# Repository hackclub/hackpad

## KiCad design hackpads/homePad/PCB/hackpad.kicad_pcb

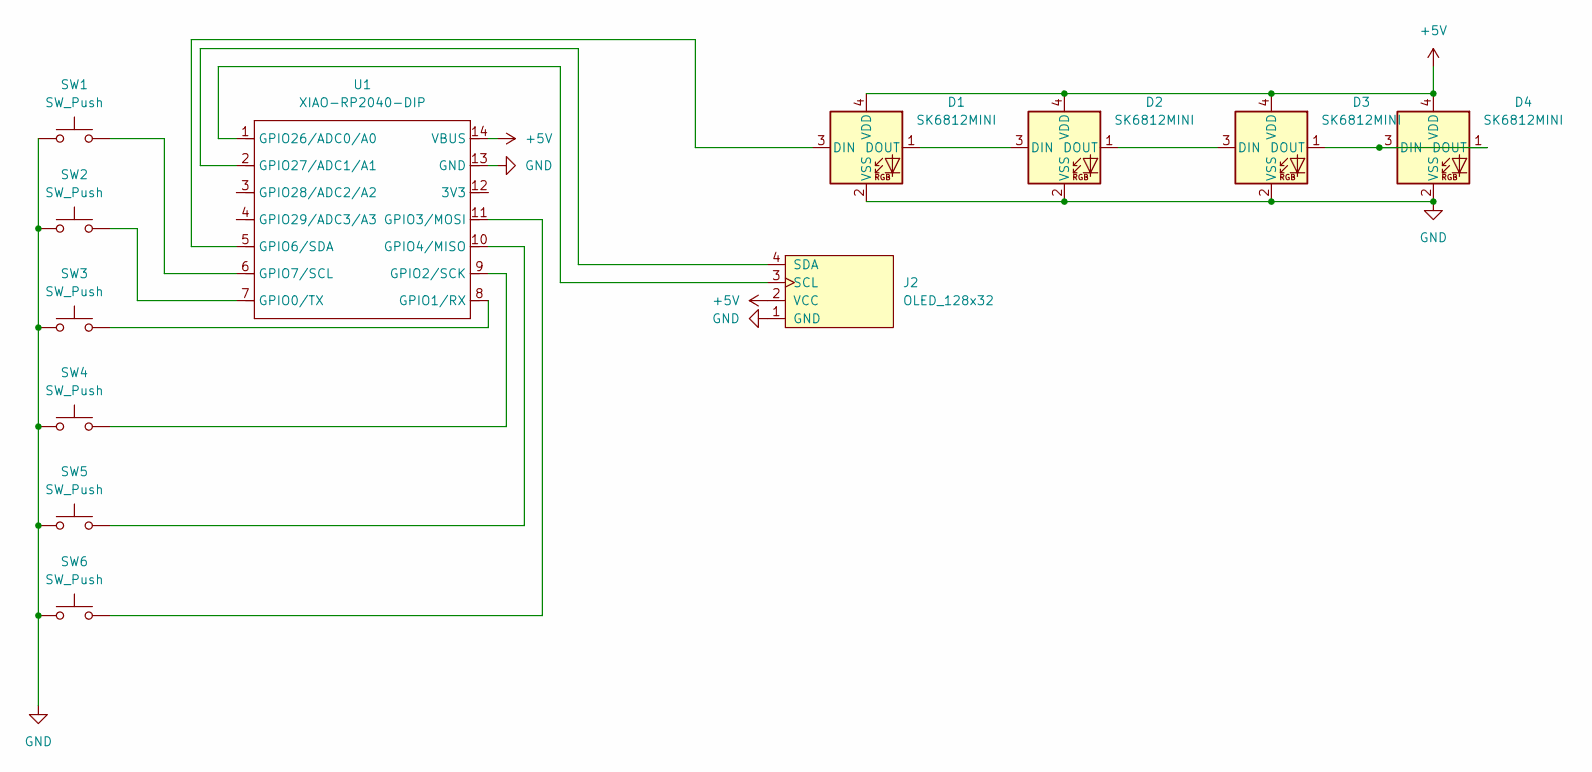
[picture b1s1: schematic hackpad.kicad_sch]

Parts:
D1, D2, D3, D4: SK6812MINI; LED_SK6812MINI_PLCC4_3.5x3.5mm_P1.75mm
J2: OLED_128x32
SW1, SW2, SW3, SW4, SW5, SW6: SW_Push; SW_Cherry_MX_1.00u_PCB
U1: XIAO-RP2040-DIP

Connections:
+5V: D1.4 (VDD), D2.4 (VDD), D3.4 (VDD), D4.4 (VDD), J2.2 (VCC), U1.14 (VBUS)
GND: D1.2 (VSS), D2.2 (VSS), D3.2 (VSS), D4.2 (VSS), J2.1 (GND), SW1.1, SW2.1, SW3.1, SW4.1, SW5.1, SW6.1, U1.13 (GND)
unnamed: D1.3 (DIN), U1.5 (GPIO6/SDA)
unnamed: D1.1 (DOUT), D2.3 (DIN)
unnamed: D2.1 (DOUT), D3.3 (DIN)
unnamed: D3.1 (DOUT), D4.1 (DOUT), D4.3 (DIN)
unnamed: J2.3 (SCL), U1.1 (GPIO26/ADC0/A0)
unnamed: J2.4 (SDA), U1.2 (GPIO27/ADC1/A1)
unnamed: SW2.2, U1.7 (GPIO0/TX)
unnamed: SW3.2, U1.8 (GPIO1/RX)
unnamed: SW4.2, U1.9 (GPIO2/SCK)
unnamed: SW6.2, U1.11 (GPIO3/MOSI)
unnamed: SW5.2, U1.10 (GPIO4/MISO)
unnamed: SW1.2, U1.6 (GPIO7/SCL)

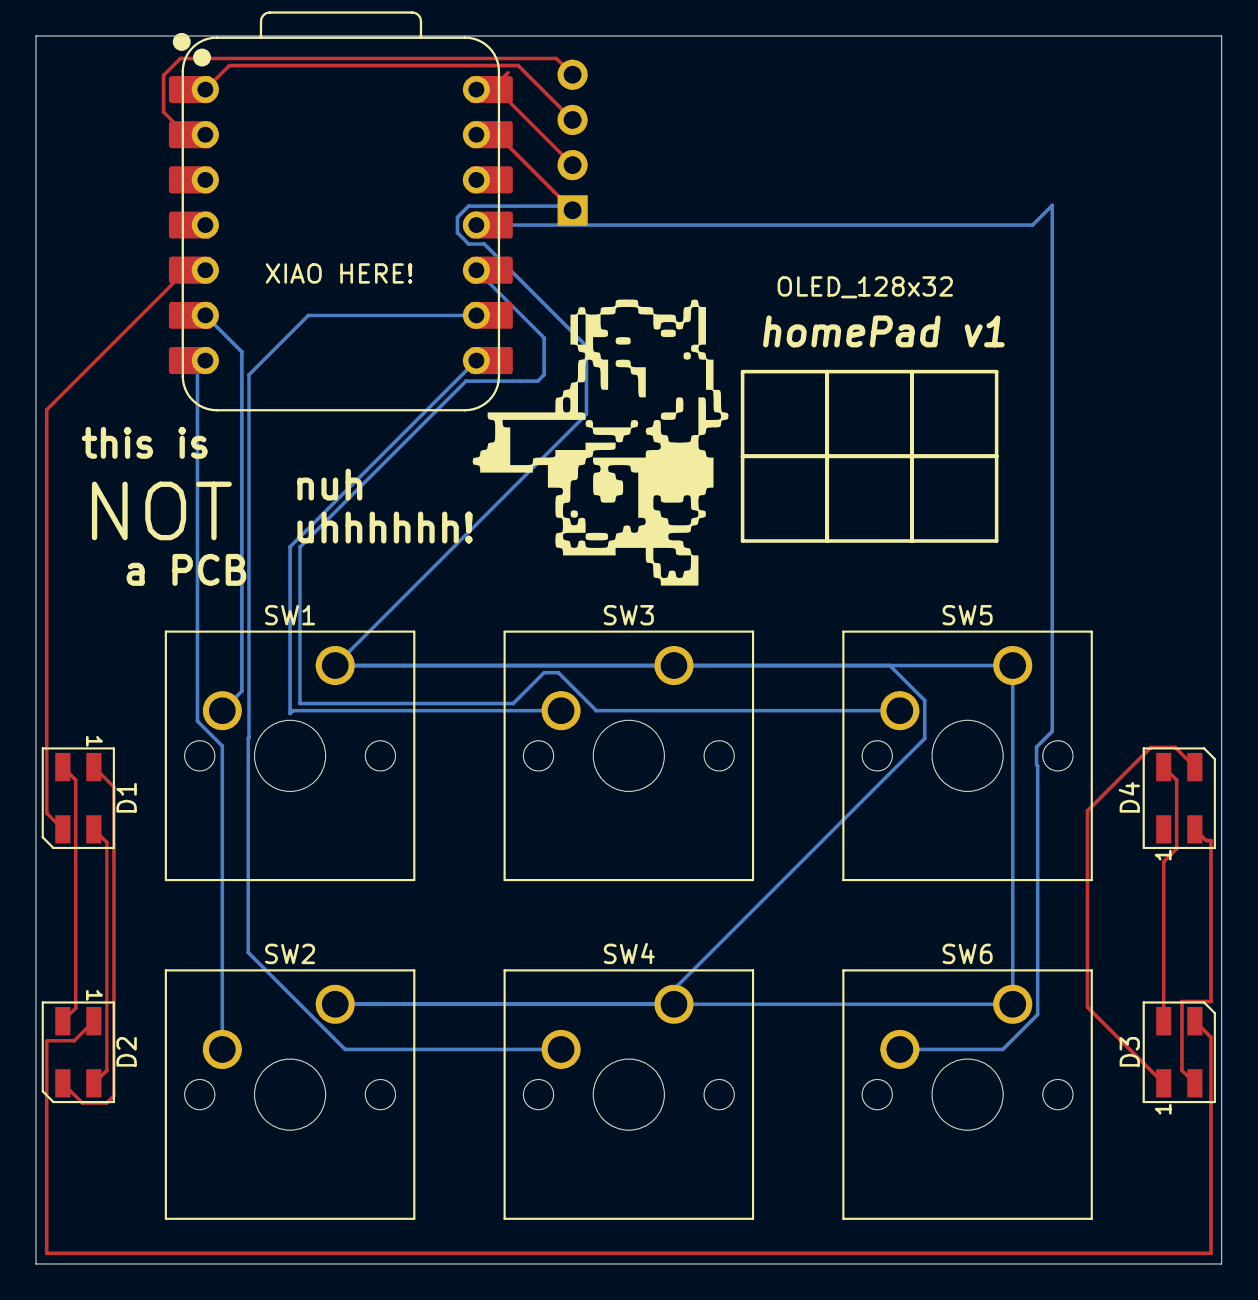
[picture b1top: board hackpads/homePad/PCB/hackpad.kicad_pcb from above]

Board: 2 copper layers, 66.7 x 69.1 mm, 12 parts (0 on the bottom side), 14 nets.

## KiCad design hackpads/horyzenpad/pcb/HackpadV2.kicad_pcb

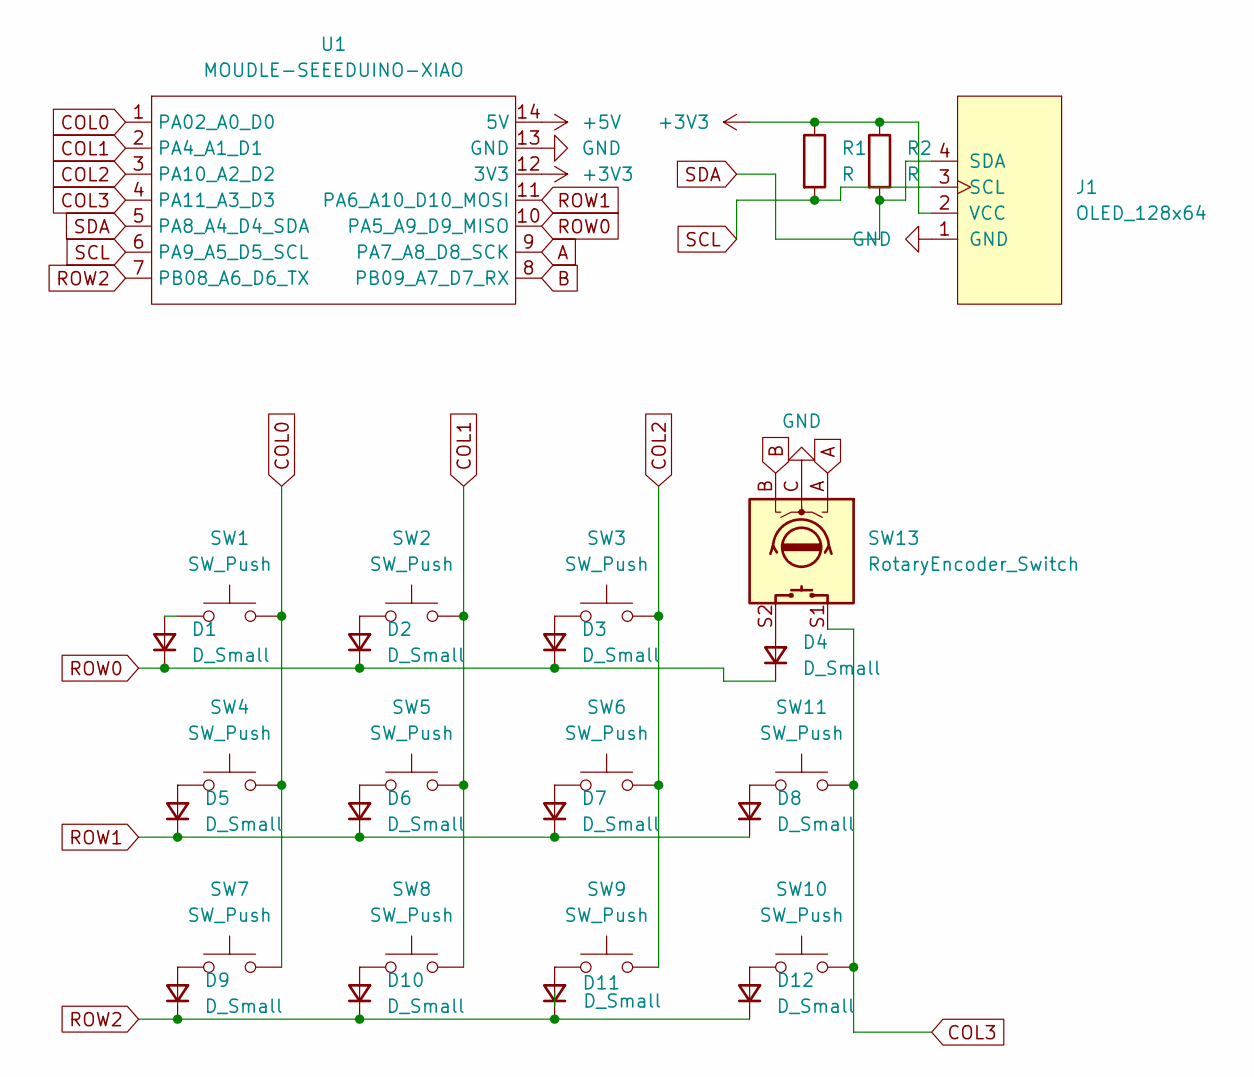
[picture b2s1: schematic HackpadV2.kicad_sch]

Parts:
D1, D2, D3, D4, D5, D6, D7, D8, D9, D10, D11, D12: D_Small; Diode_DO-35
J1: OLED_128x64
R1, R2: R; R_Axial_DIN0204_L3.6mm_D1.6mm_P7.62mm_Horizontal
SW1, SW2, SW3, SW4, SW5, SW6, SW7, SW8, SW9, SW10, SW11: SW_Push; SW_Cherry_MX_1.00u_PCB
SW13: RotaryEncoder_Switch; RotaryEncoder_Alps_EC11E-Switch_Vertical_H20mm
U1: MOUDLE-SEEEDUINO-XIAO; XIAO-Generic-Hybrid-14P-2.54-21X17.8MM

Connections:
+3V3: J1.2 (VCC), R1.1, R2.1, U1.12 (3V3)
+5V: U1.14 (5V)
A: SW13.A, U1.9 (PA7_A8_D8_SCK)
B: SW13.B, U1.8 (PB09_A7_D7_RX)
COL0: SW1.2, SW4.2, SW7.2, U1.1 (PA02_A0_D0)
COL1: SW2.2, SW5.2, SW8.2, U1.2 (PA4_A1_D1)
COL2: SW3.2, SW6.2, SW9.2, U1.3 (PA10_A2_D2)
COL3: SW10.2, SW11.2, SW13.S1, U1.4 (PA11_A3_D3)
GND: J1.1 (GND), SW13.C, U1.13 (GND)
unnamed: D1.2 (A), SW1.1
unnamed: D2.2 (A), SW2.1
unnamed: D3.2 (A), SW3.1
unnamed: D4.2 (A), SW13.S2
unnamed: D5.2 (A), SW4.1
unnamed: D6.2 (A), SW5.1
unnamed: D7.2 (A), SW6.1
unnamed: D8.2 (A), SW11.1
unnamed: D9.2 (A), SW7.1
unnamed: D10.2 (A), SW8.1
unnamed: D11.2 (A), SW9.1
unnamed: D12.2 (A), SW10.1
ROW0: D1.1 (K), D2.1 (K), D3.1 (K), D4.1 (K), U1.10 (PA5_A9_D9_MISO)
ROW1: D5.1 (K), D6.1 (K), D7.1 (K), D8.1 (K), U1.11 (PA6_A10_D10_MOSI)
ROW2: D9.1 (K), D10.1 (K), D11.1 (K), D12.1 (K), U1.7 (PB08_A6_D6_TX)
SCL: J1.3 (SCL), R1.2, U1.6 (PA9_A5_D5_SCL)
SDA: J1.4 (SDA), R2.2, U1.5 (PA8_A4_D4_SDA)

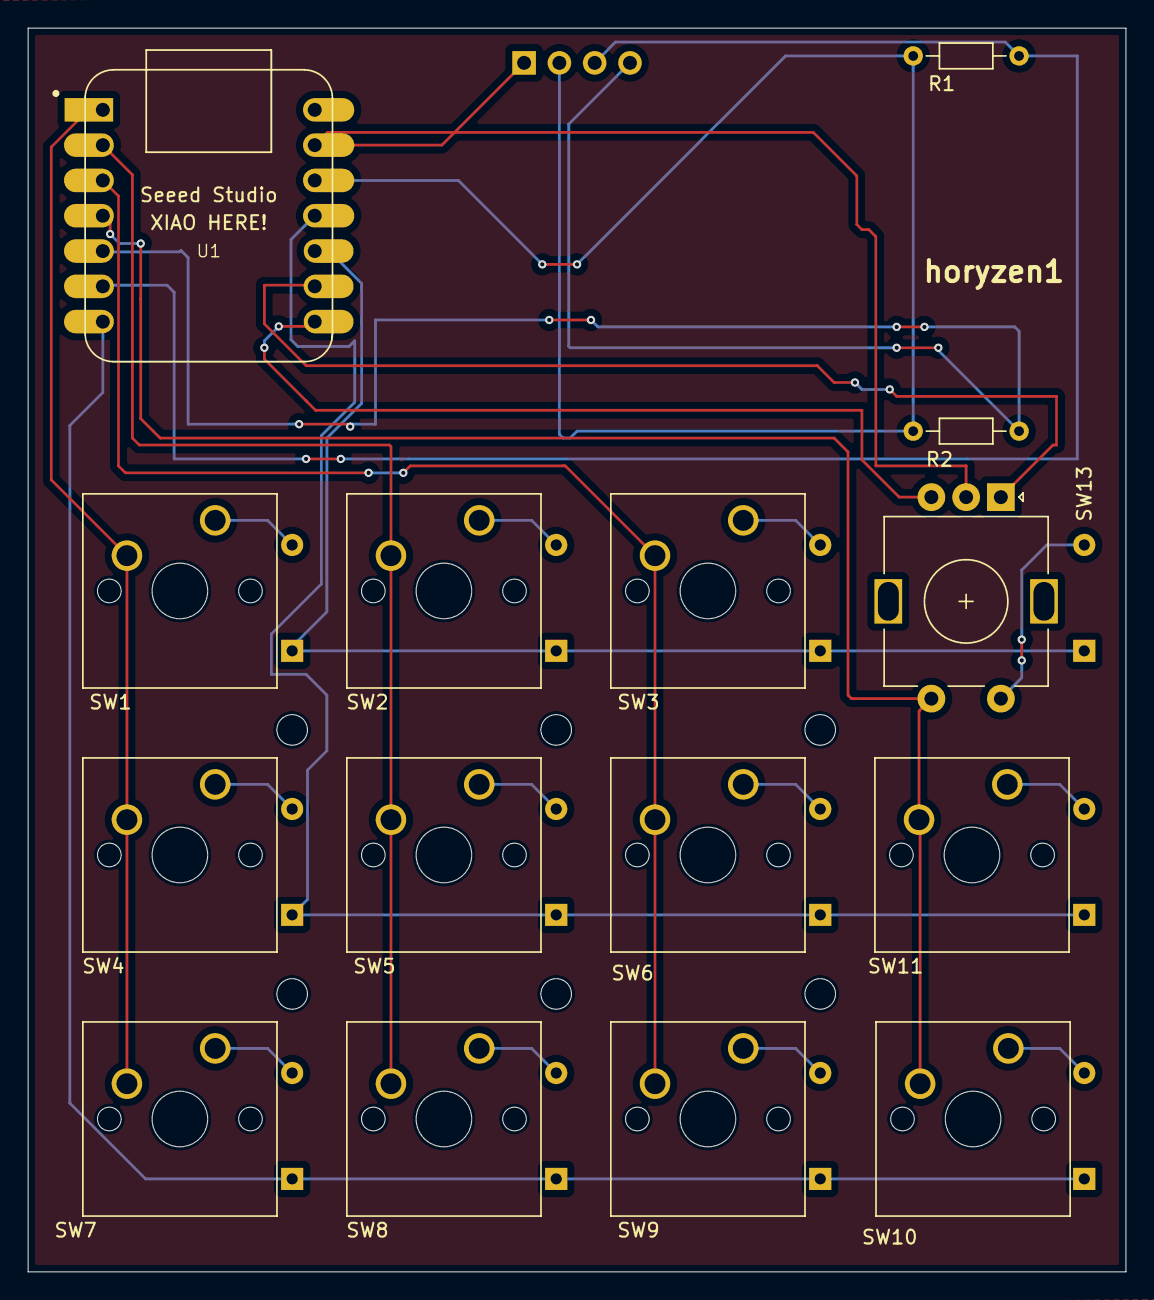
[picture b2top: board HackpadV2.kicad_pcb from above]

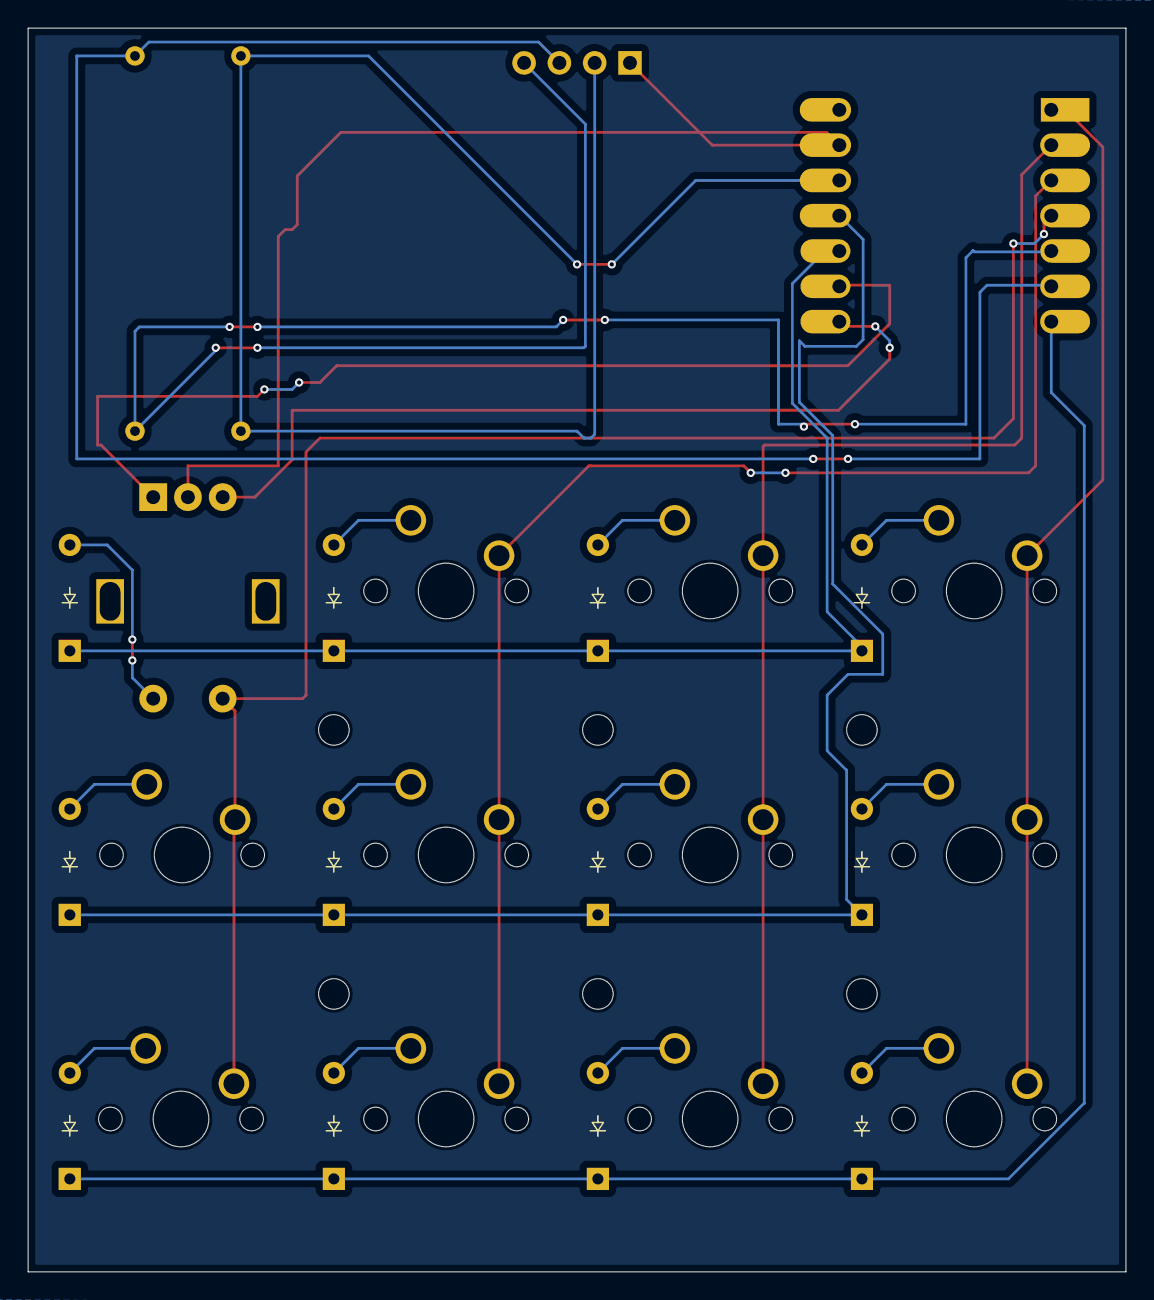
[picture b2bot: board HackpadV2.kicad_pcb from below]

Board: 2 copper layers, 79.0 x 89.5 mm, 29 parts (12 on the bottom side), 25 nets.

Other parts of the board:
horyzen1: LOGO; finaled

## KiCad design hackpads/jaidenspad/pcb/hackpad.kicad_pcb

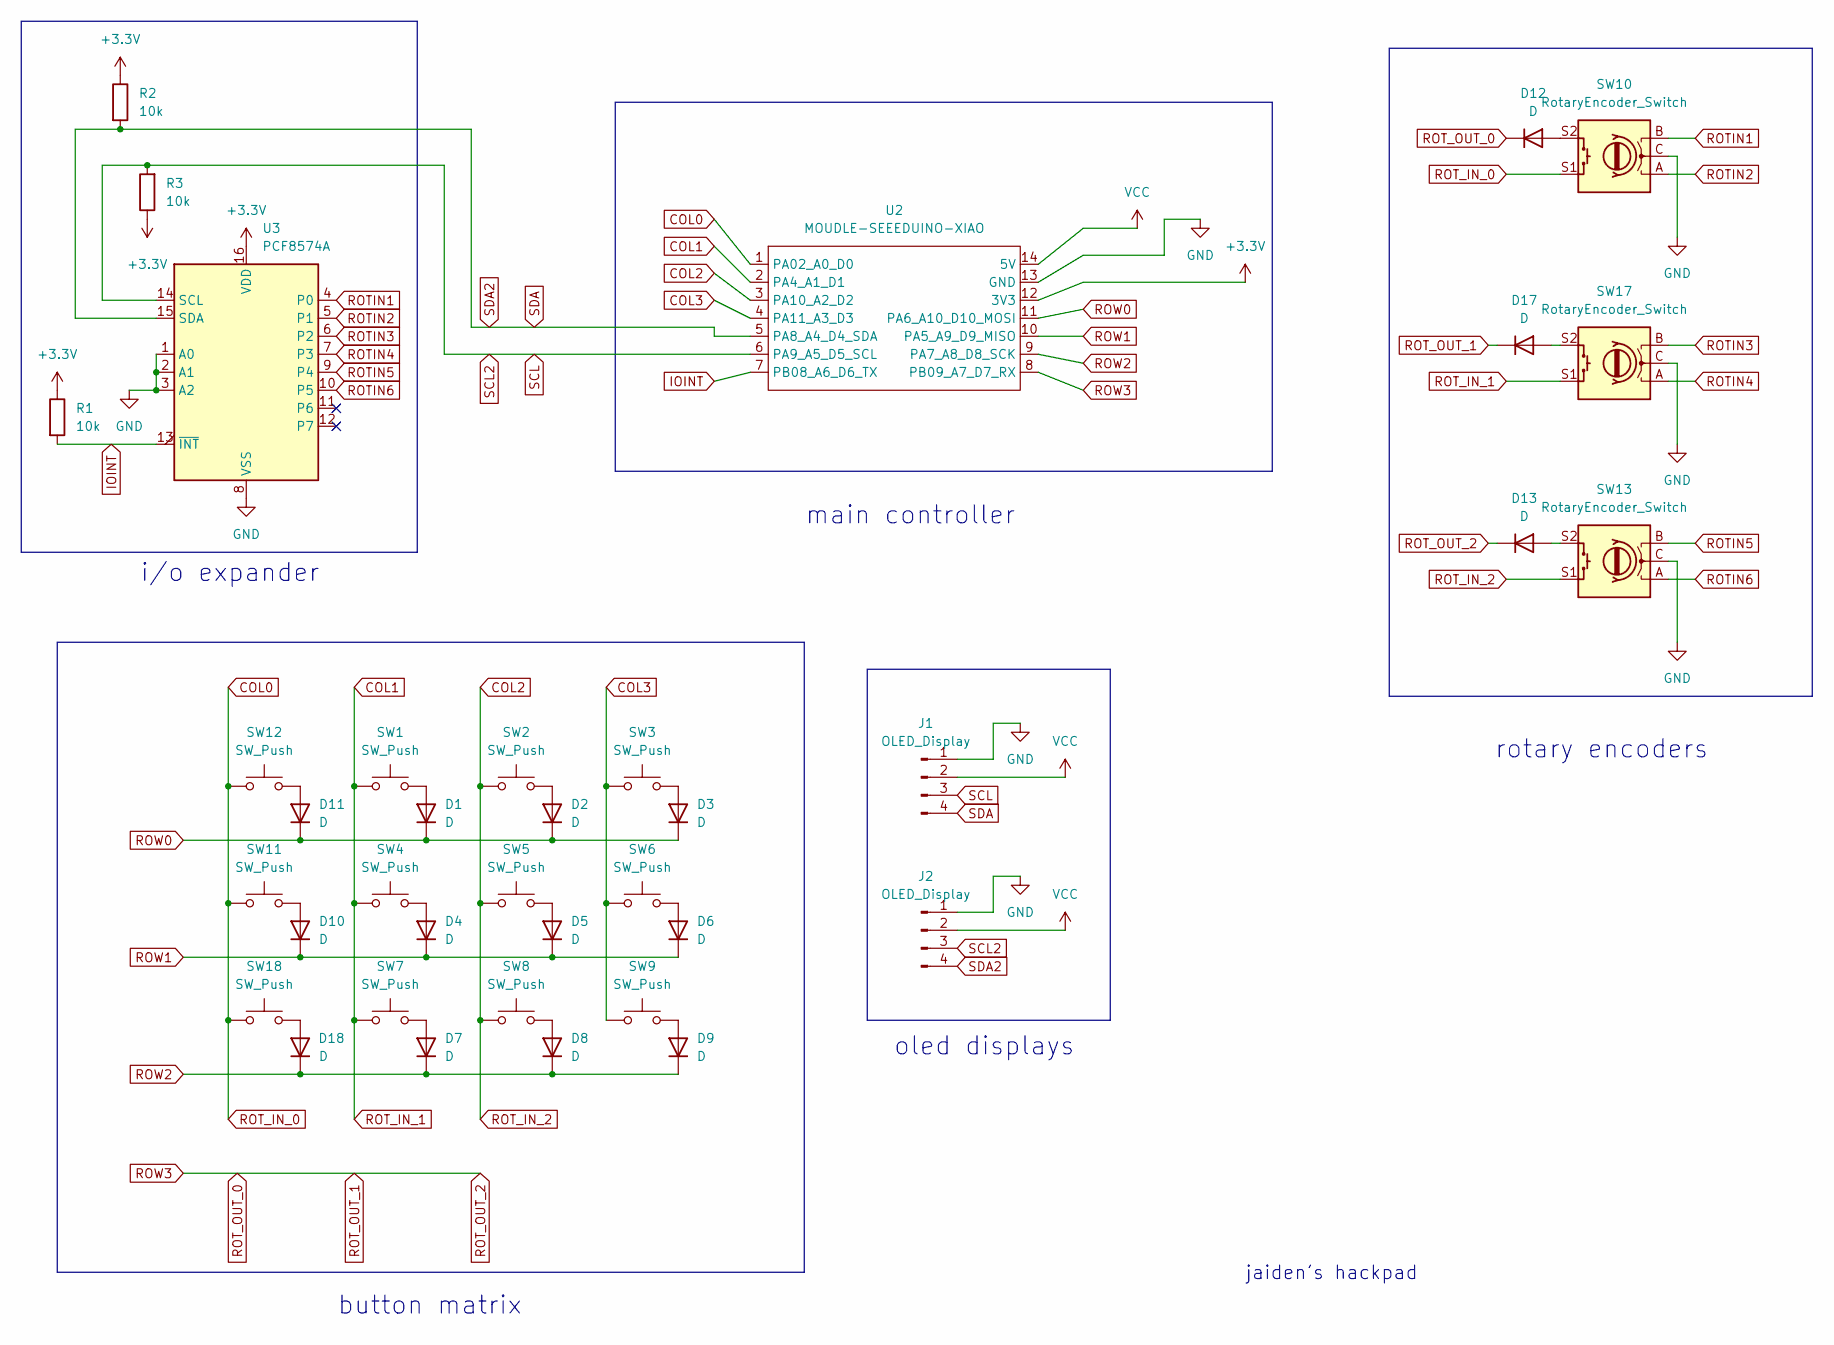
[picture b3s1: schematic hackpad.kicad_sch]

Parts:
D1, D2, D3, D4, D5, D6, D7, D8, D9, D10, D11, D12, D13, D17, D18: D; D_DO-35_SOD27_P7.62mm_Horizontal
J1, J2: OLED_Display; SSD1306-0.91-OLED-4pin-128x32
R1, R2, R3: 10k; R_Axial_DIN0204_L3.6mm_D1.6mm_P1.90mm_Vertical
SW1, SW2, SW3, SW4, SW5, SW6, SW7, SW8, SW9, SW11, SW12, SW18: SW_Push; SW_Cherry_MX_1.00u_PCB
SW10, SW13, SW17: RotaryEncoder_Switch; RotaryEncoder_Alps_EC11E-Switch_Vertical_H20mm
U2: MOUDLE-SEEEDUINO-XIAO; XIAO-Generic-Hybrid-14P-2.54-21X17.8MM
U3: PCF8574A; DIP-16_W7.62mm

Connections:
+3.3V: R1.1, R2.1, R3.1, U2.12 (3V3), U3.16 (VDD)
COL0: SW10.S1, SW11.1, SW12.1, SW18.1, U2.1 (PA02_A0_D0)
COL1: SW1.1, SW4.1, SW7.1, SW17.S1, U2.2 (PA4_A1_D1)
COL2: SW2.1, SW5.1, SW8.1, SW13.S1, U2.3 (PA10_A2_D2)
COL3: SW3.1, SW6.1, SW9.1, U2.4 (PA11_A3_D3)
GND: J1.1, J2.1, SW10.C, SW13.C, SW17.C, U2.13 (GND), U3.1 (A0), U3.2 (A1), U3.3 (A2), U3.8 (VSS)
IOINT: R1.2, U2.7 (PB08_A6_D6_TX), U3.13 (~INT)
unnamed: D1.2 (A), SW1.2
unnamed: D2.2 (A), SW2.2
unnamed: D3.2 (A), SW3.2
unnamed: D4.2 (A), SW4.2
unnamed: D5.2 (A), SW5.2
unnamed: D6.2 (A), SW6.2
unnamed: D7.2 (A), SW7.2
unnamed: D8.2 (A), SW8.2
unnamed: D9.2 (A), SW9.2
unnamed: D10.2 (A), SW11.2
unnamed: D11.2 (A), SW12.2
unnamed: D12.2 (A), SW10.S2
unnamed: D13.2 (A), SW13.S2
unnamed: D17.2 (A), SW17.S2
unnamed: D18.2 (A), SW18.2
ROTIN1: SW10.B, U3.4 (P0)
ROTIN2: SW10.A, U3.5 (P1)
ROTIN3: SW17.B, U3.6 (P2)
ROTIN4: SW17.A, U3.7 (P3)
ROTIN5: SW13.B, U3.9 (P4)
ROTIN6: SW13.A, U3.10 (P5)
ROT_OUT_0: D12.1 (K), D13.1 (K), D17.1 (K), U2.8 (PB09_A7_D7_RX)
ROW0: D1.1 (K), D2.1 (K), D3.1 (K), D11.1 (K), U2.11 (PA6_A10_D10_MOSI)
ROW1: D4.1 (K), D5.1 (K), D6.1 (K), D10.1 (K), U2.10 (PA5_A9_D9_MISO)
ROW2: D7.1 (K), D8.1 (K), D9.1 (K), D18.1 (K), U2.9 (PA7_A8_D8_SCK)
SCL: J1.3, J2.3, R3.2, U2.6 (PA9_A5_D5_SCL), U3.14 (SCL)
SDA: J1.4, J2.4, R2.2, U2.5 (PA8_A4_D4_SDA), U3.15 (SDA)
VCC: J1.2, J2.2, U2.14 (5V)

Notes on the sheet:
jaiden's hackpad
oled displays
i/o expander
rotary encoders
main controller
button matrix

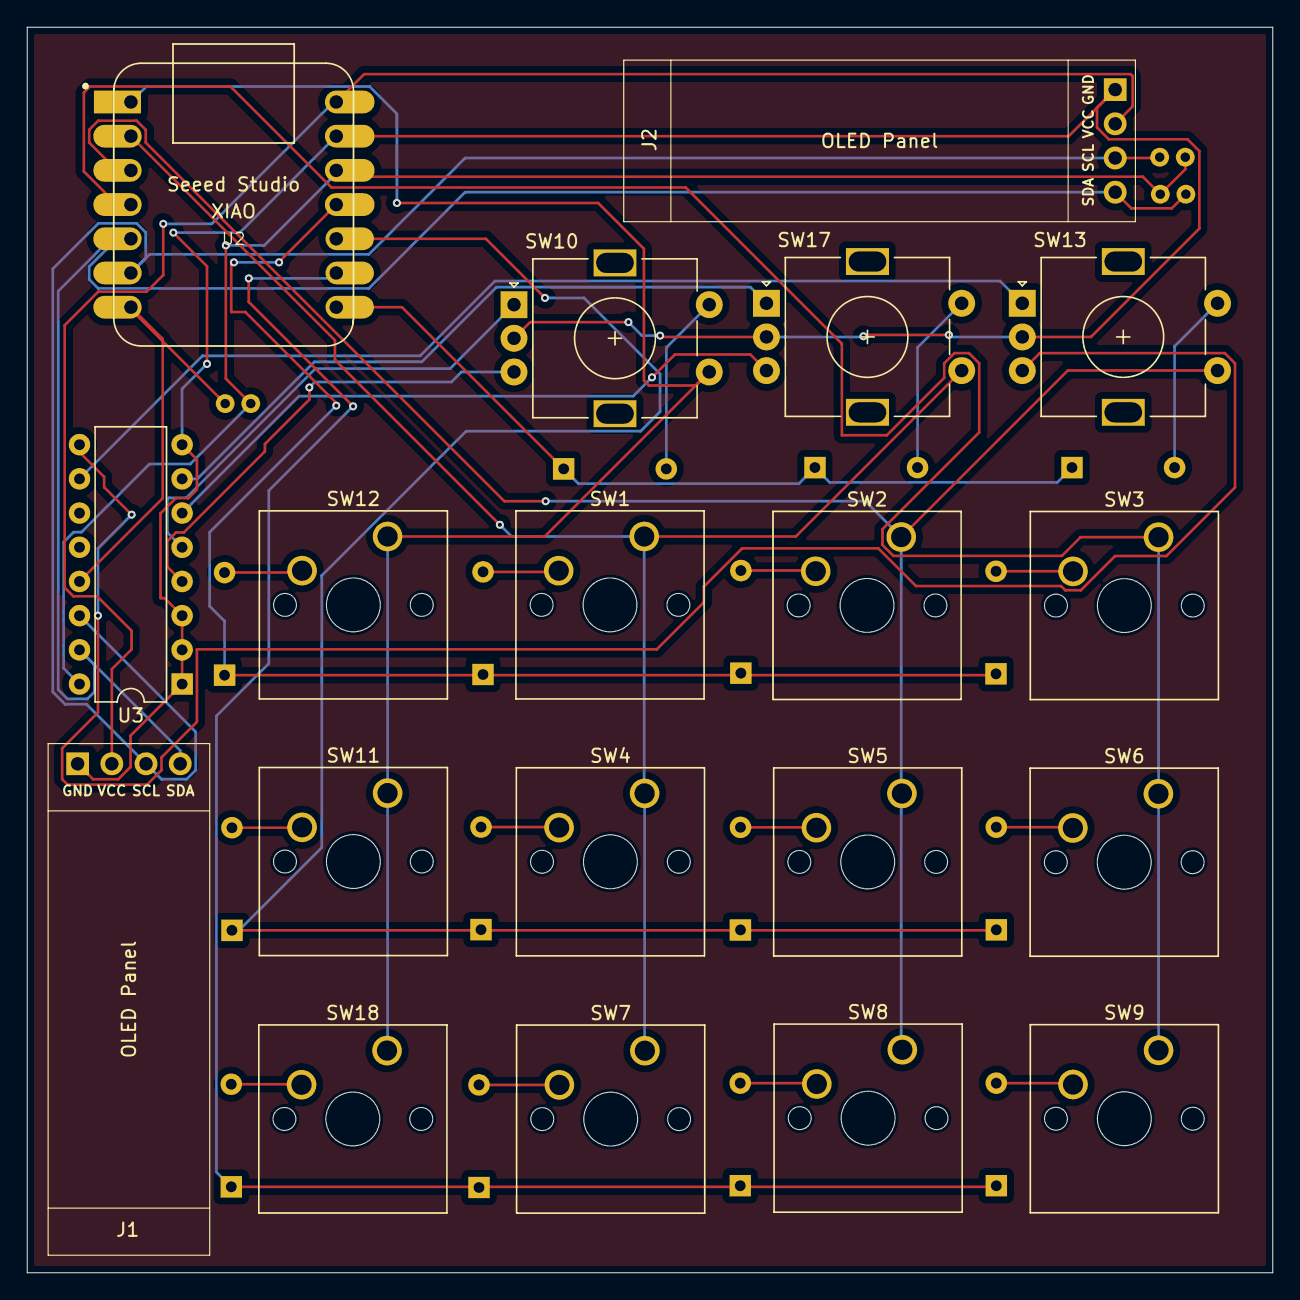
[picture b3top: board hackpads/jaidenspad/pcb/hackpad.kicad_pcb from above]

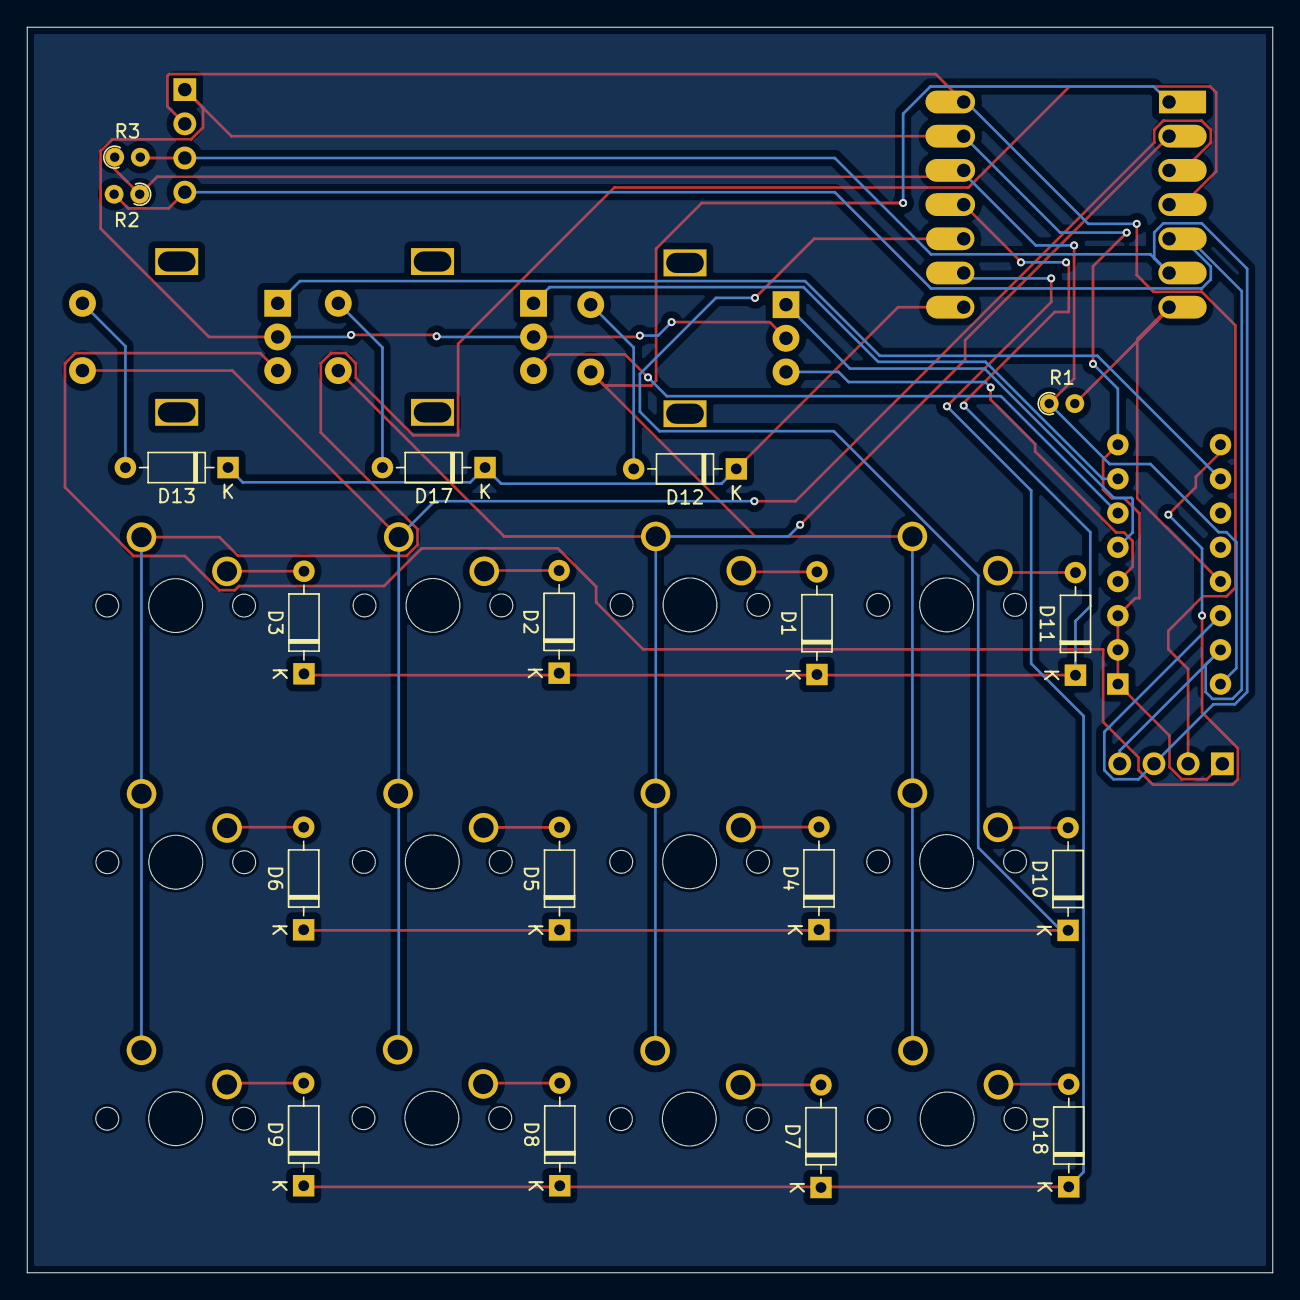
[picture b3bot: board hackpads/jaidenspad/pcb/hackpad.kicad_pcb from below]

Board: 2 copper layers, 92.5 x 92.5 mm, 37 parts (18 on the bottom side), 35 nets.

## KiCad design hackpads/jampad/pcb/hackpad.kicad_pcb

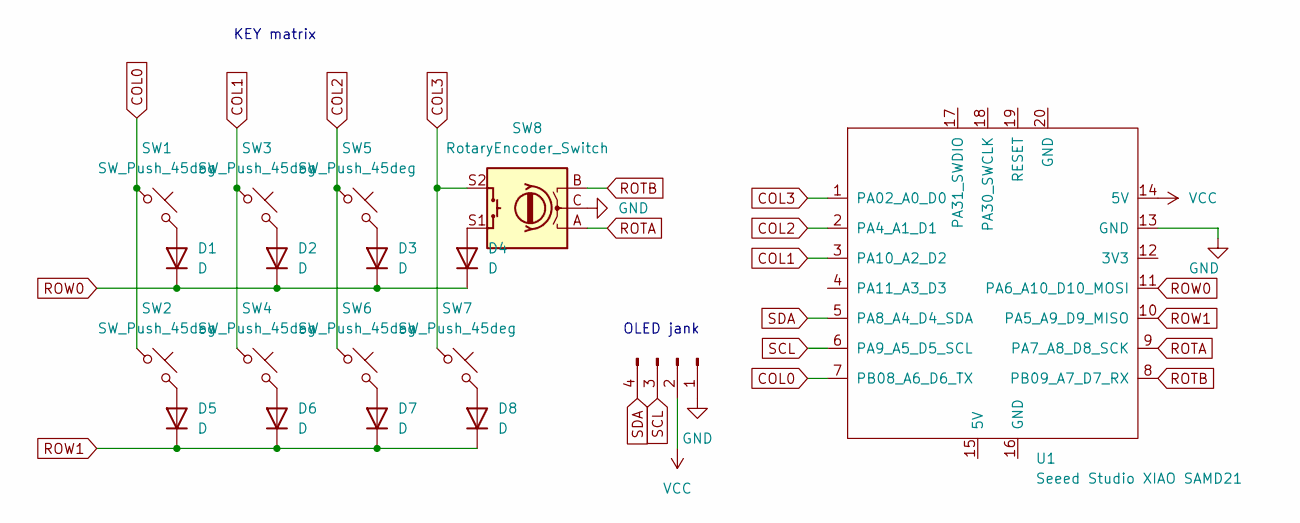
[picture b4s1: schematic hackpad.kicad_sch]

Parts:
D1, D2, D3, D4, D5, D6, D7, D8: D; D_DO-35_SOD27_P7.62mm_Horizontal
O1: OLEd; SSD1306-0.91-OLED-4pin-128x32
SW1, SW2, SW3, SW4, SW5, SW6, SW7: SW_Push_45deg; SW_Cherry_MX_1.00u_PCB
SW8: RotaryEncoder_Switch; RotaryEncoder_Alps_EC11E-Switch_Vertical_H20mm
U1: Seeed Studio XIAO SAMD21; XIAO-Generic-Thruhole-14P-2.54-21X17.8MM

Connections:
COL0: SW1.1, SW2.1, U1.7 (PB08_A6_D6_TX)
COL1: SW3.1, SW4.1, U1.3 (PA10_A2_D2)
COL2: SW5.1, SW6.1, U1.2 (PA4_A1_D1)
COL3: SW7.1, SW8.S2, U1.1 (PA02_A0_D0)
GND: O1.1, SW8.C, U1.13 (GND)
unnamed: D1.2 (A), SW1.2
unnamed: D2.2 (A), SW3.2
unnamed: D3.2 (A), SW5.2
unnamed: D4.2 (A), SW8.S1
unnamed: D5.2 (A), SW2.2
unnamed: D6.2 (A), SW4.2
unnamed: D7.2 (A), SW6.2
unnamed: D8.2 (A), SW7.2
ROTA: SW8.A, U1.9 (PA7_A8_D8_SCK)
ROTB: SW8.B, U1.8 (PB09_A7_D7_RX)
ROW0: D1.1 (K), D2.1 (K), D3.1 (K), D4.1 (K), U1.11 (PA6_A10_D10_MOSI)
ROW1: D5.1 (K), D6.1 (K), D7.1 (K), D8.1 (K), U1.10 (PA5_A9_D9_MISO)
SCL: O1.3, U1.6 (PA9_A5_D5_SCL)
SDA: O1.4, U1.5 (PA8_A4_D4_SDA)
VCC: O1.2, U1.14 (5V)

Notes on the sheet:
OLED jank
KEY matrix

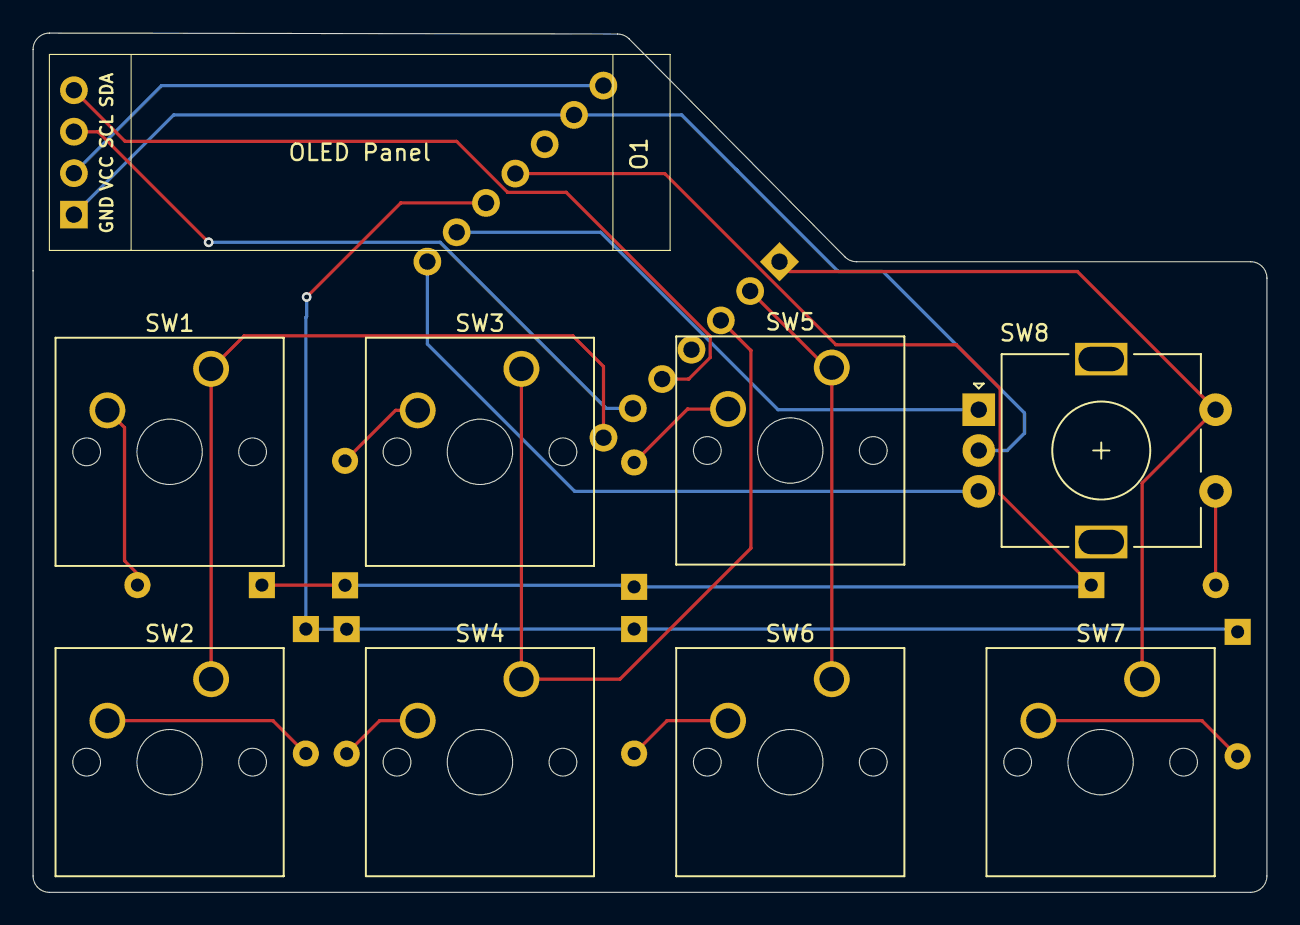
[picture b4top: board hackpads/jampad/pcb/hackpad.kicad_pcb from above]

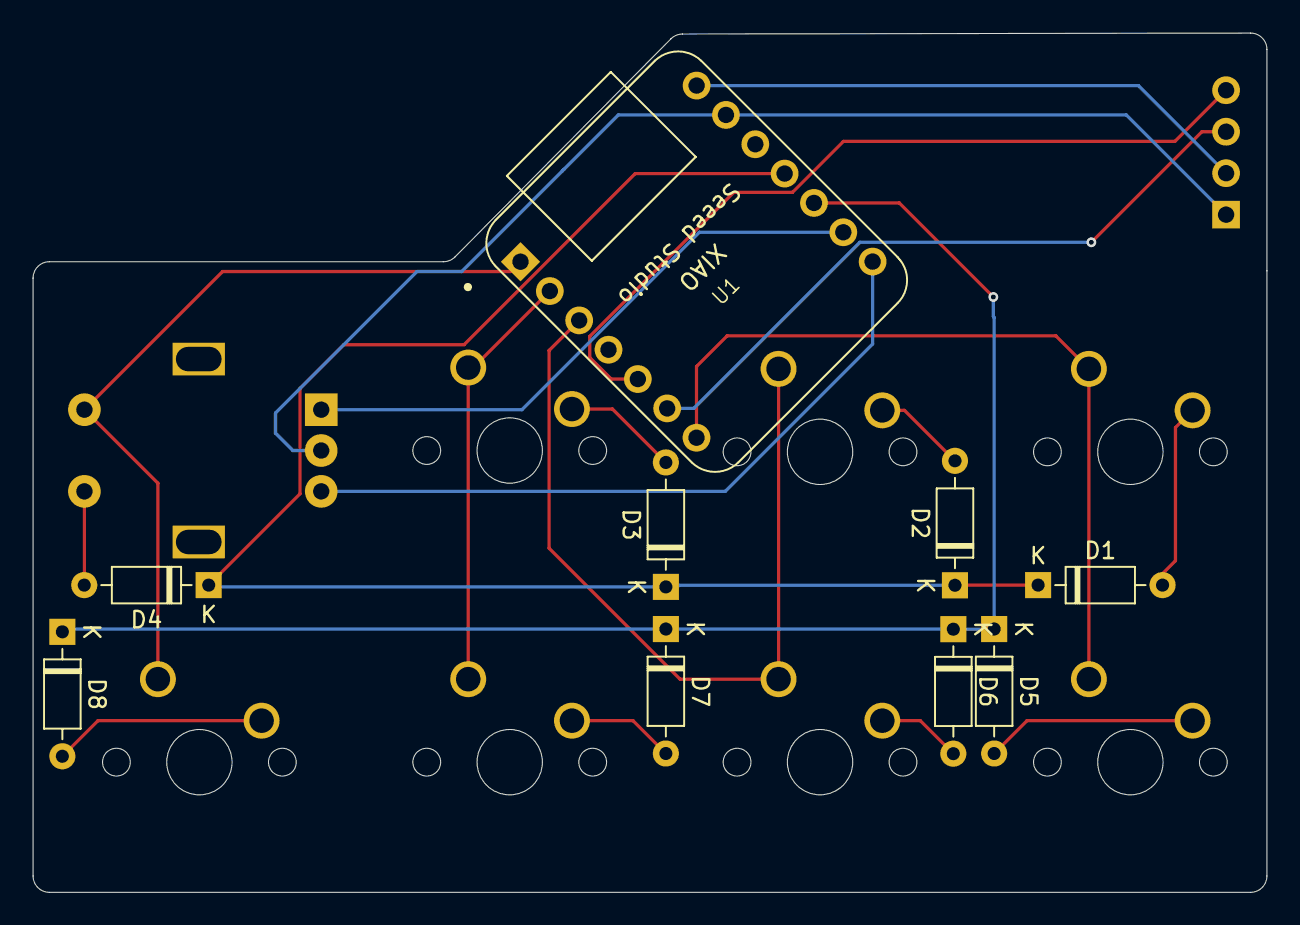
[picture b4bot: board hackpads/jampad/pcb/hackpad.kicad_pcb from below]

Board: 2 copper layers, 75.5 x 52.6 mm, 18 parts (9 on the bottom side), 20 nets.

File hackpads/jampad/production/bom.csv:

Designator,Footprint,Quantity,Value,LCSC Part #
"D1, D2, D3, D4, D5, D6, D7, D8",D_DO-35_SOD27_P7.62mm_Horizontal,8,D,
O1,SSD1306-0.91-OLED-4pin-128x32,1,OLEd,
"SW1, SW2, SW3, SW4, SW5, SW6, SW7",SW_Cherry_MX_1.00u_PCB,7,SW_Push_45deg,
SW8,RotaryEncoder_Alps_EC11E-Switch_Vertical_H20mm,1,RotaryEncoder_Switch,
U1,XIAO-Generic-Thruhole-14P-2.54-21X17.8MM,1,Seeed Studio XIAO SAMD21,
